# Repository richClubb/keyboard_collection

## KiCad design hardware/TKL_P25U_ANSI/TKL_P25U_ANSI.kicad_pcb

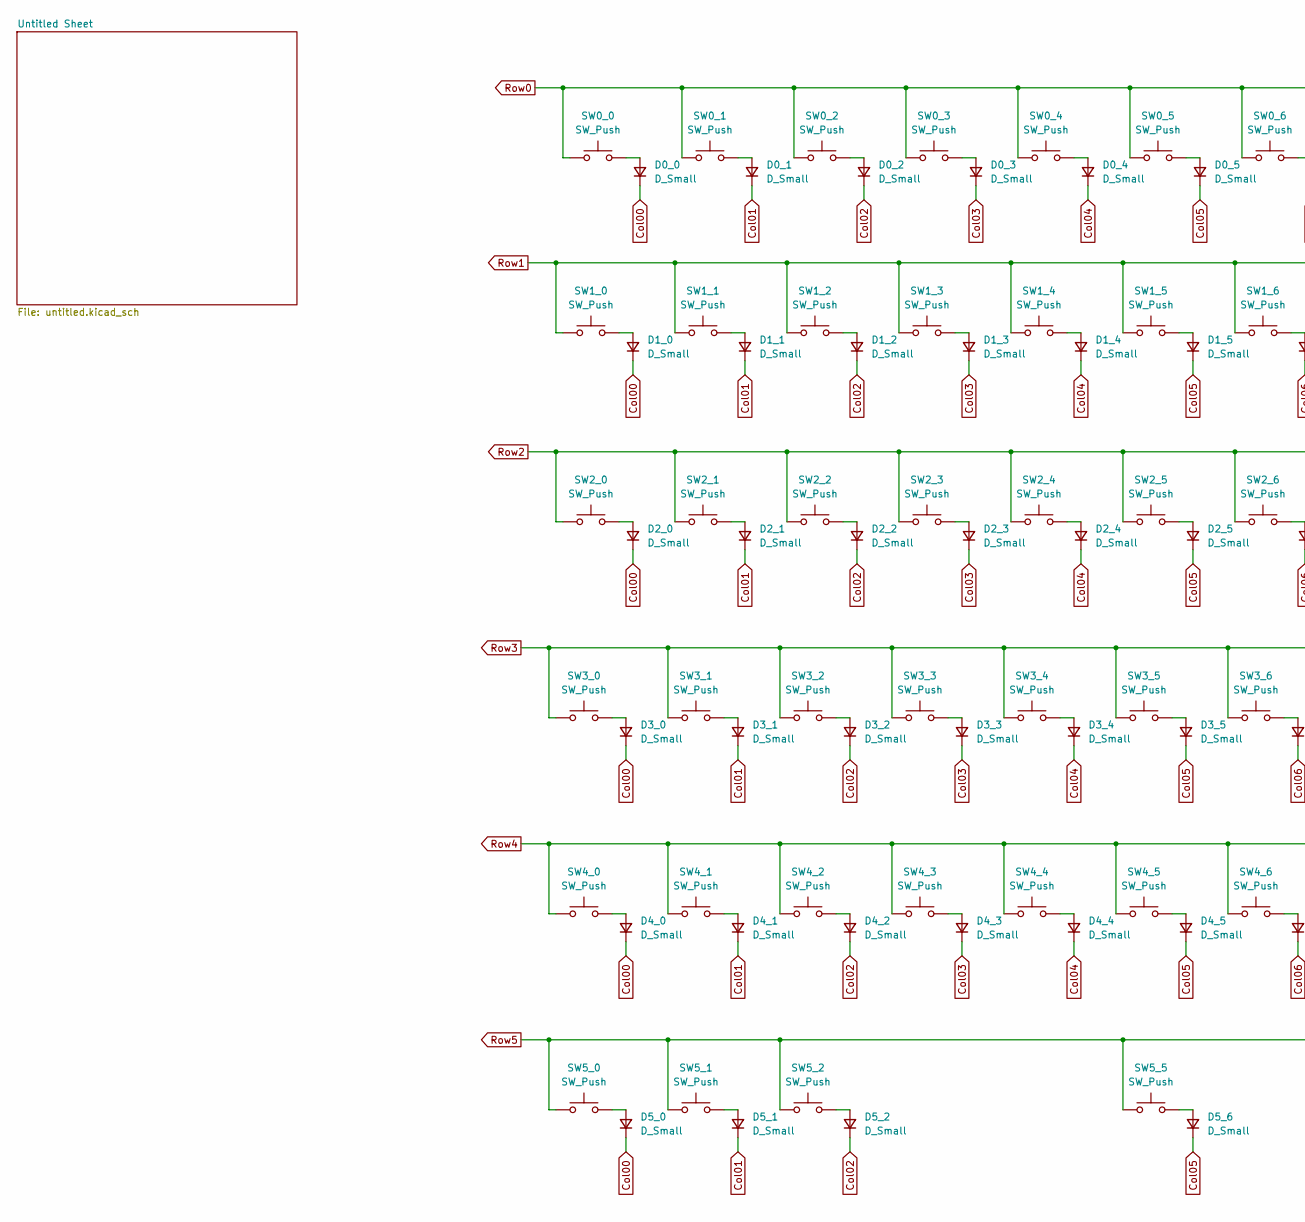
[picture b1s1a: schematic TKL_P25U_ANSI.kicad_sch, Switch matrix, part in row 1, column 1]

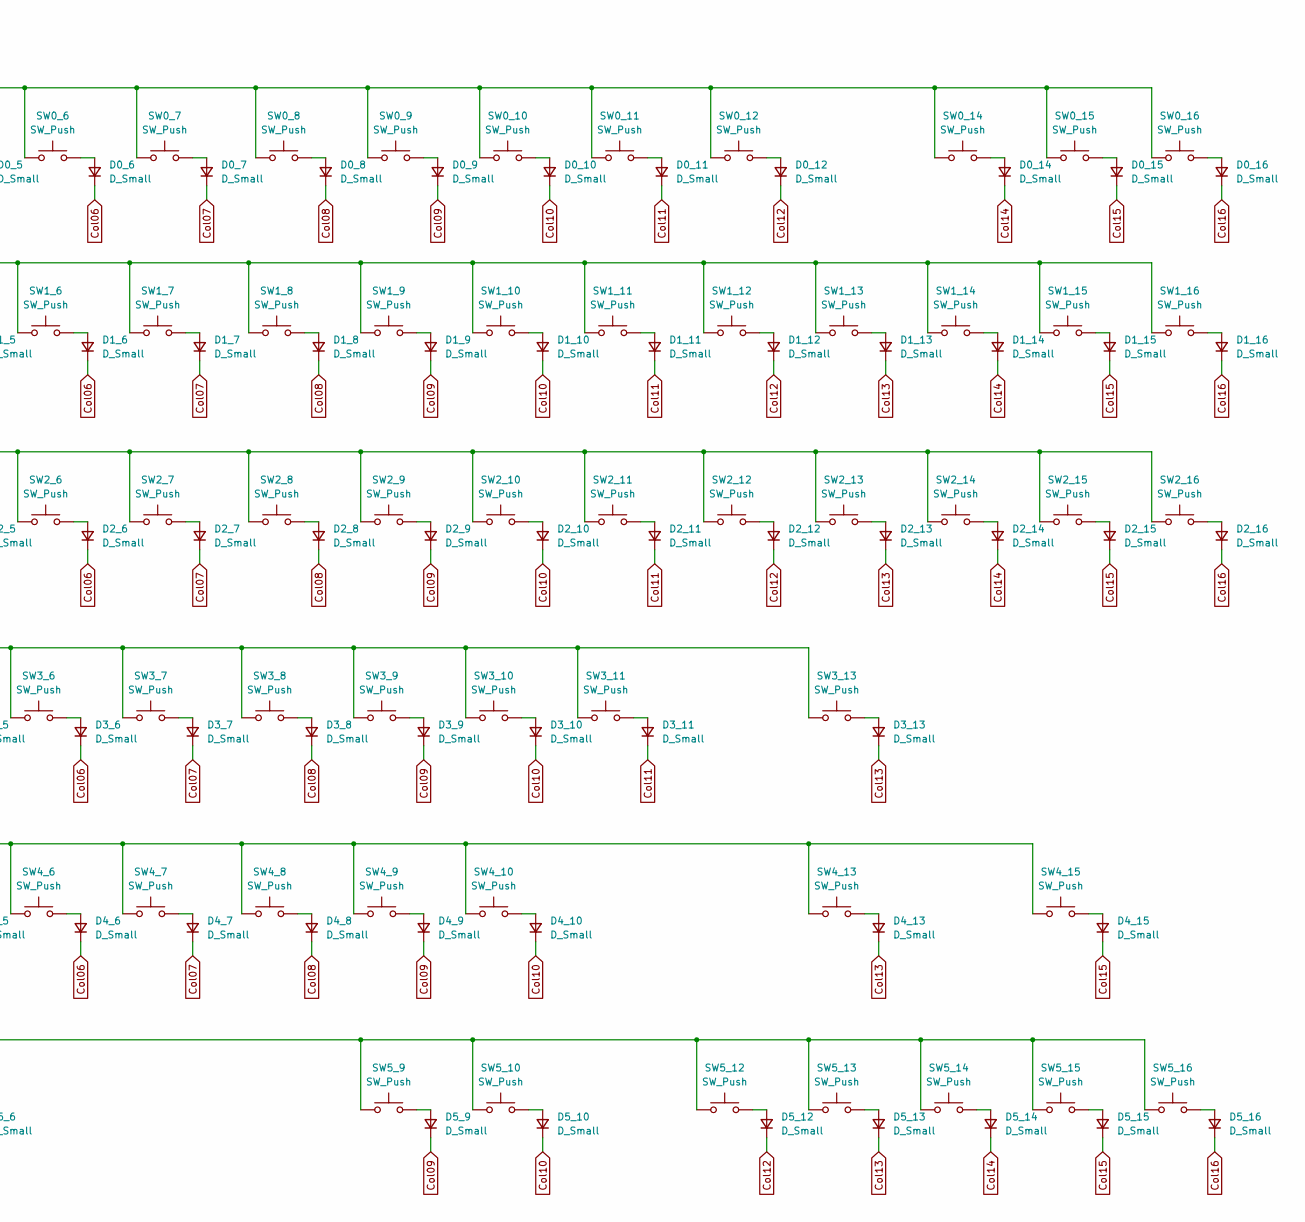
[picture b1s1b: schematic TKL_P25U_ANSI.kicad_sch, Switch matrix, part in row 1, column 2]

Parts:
D0_0, D0_1, D0_2, D0_3, D0_4, D0_5, D0_6, D0_7, D0_8, D0_9, D0_10, D0_11, D0_12, D0_14, D0_15, D0_16, D1_0, D1_1, D1_2, D1_3, D1_4, D1_5, D1_6, D1_7, D1_8, D1_9, D1_10, D1_11, D1_12, D1_13, D1_14, D1_15, D1_16, D2_0, D2_1, D2_2, D2_3, D2_4, D2_5, D2_6, D2_7, D2_8, D2_9, D2_10, D2_11, D2_12, D2_13, D2_14, D2_15, D2_16, D3_0, D3_1, D3_2, D3_3, D3_4, D3_5, D3_6, D3_7, D3_8, D3_9, D3_10, D3_11, D3_13, D4_0, D4_1, D4_2, D4_3, D4_4, D4_5, D4_6, D4_7, D4_8, D4_9, D4_10, D4_13, D4_15, D5_0, D5_1, D5_2, D5_6, D5_9, D5_10, D5_12, D5_13, D5_14, D5_15, D5_16: D_Small; D_0603_1608Metric
SW0_0, SW0_1, SW0_2, SW0_3, SW0_4, SW0_5, SW0_6, SW0_7, SW0_8, SW0_9, SW0_10, SW0_11, SW0_12, SW0_14, SW0_15, SW0_16, SW1_0, SW1_1, SW1_2, SW1_3, SW1_4, SW1_5, SW1_6, SW1_7, SW1_8, SW1_9, SW1_10, SW1_11, SW1_12, SW1_14, SW1_15, SW1_16, SW2_1, SW2_2, SW2_3, SW2_4, SW2_5, SW2_6, SW2_7, SW2_8, SW2_9, SW2_10, SW2_11, SW2_12, SW2_14, SW2_15, SW2_16, SW3_1, SW3_2, SW3_3, SW3_4, SW3_5, SW3_6, SW3_7, SW3_8, SW3_9, SW3_10, SW3_11, SW4_1, SW4_2, SW4_3, SW4_4, SW4_5, SW4_6, SW4_7, SW4_8, SW4_9, SW4_10, SW4_15, SW5_14, SW5_15, SW5_16: SW_Push; SW_Cherry_MX_1.00u_PCB
SW1_13, SW4_0: SW_Push; SW_Cherry_MX_2.00u_PCB
SW2_0, SW2_13: SW_Push; SW_Cherry_MX_1.50u_PCB
SW3_0: SW_Push; SW_Cherry_MX_1.75u_PCB
SW3_13: SW_Push; SW_Cherry_MX_2.25u_PCB
SW4_13: SW_Push; SW_Cherry_MX_2.75u_PCB
SW5_0, SW5_1, SW5_2, SW5_9, SW5_10, SW5_12, SW5_13: SW_Push; SW_Cherry_MX_1.25u_PCB
SW5_5: SW_Push; SW_Cherry_MX_6.25u_PCB

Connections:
Col00: D0_0.1 (K), D1_0.1 (K), D2_0.1 (K), D3_0.1 (K), D4_0.1 (K), D5_0.1 (K); also elsewhere on the board
Col01: D0_1.1 (K), D1_1.1 (K), D2_1.1 (K), D3_1.1 (K), D4_1.1 (K), D5_1.1 (K); also elsewhere on the board
Col02: D0_2.1 (K), D1_2.1 (K), D2_2.1 (K), D3_2.1 (K), D4_2.1 (K), D5_2.1 (K); also elsewhere on the board
Col03: D0_3.1 (K), D1_3.1 (K), D2_3.1 (K), D3_3.1 (K), D4_3.1 (K); also elsewhere on the board
Col04: D0_4.1 (K), D1_4.1 (K), D2_4.1 (K), D3_4.1 (K), D4_4.1 (K); also elsewhere on the board
Col05: D0_5.1 (K), D1_5.1 (K), D2_5.1 (K), D3_5.1 (K), D4_5.1 (K), D5_6.1 (K); also elsewhere on the board
Col06: D0_6.1 (K), D1_6.1 (K), D2_6.1 (K), D3_6.1 (K), D4_6.1 (K); also elsewhere on the board
Col07: D0_7.1 (K), D1_7.1 (K), D2_7.1 (K), D3_7.1 (K), D4_7.1 (K); also elsewhere on the board
Col08: D0_8.1 (K), D1_8.1 (K), D2_8.1 (K), D3_8.1 (K), D4_8.1 (K); also elsewhere on the board
Col09: D0_9.1 (K), D1_9.1 (K), D2_9.1 (K), D3_9.1 (K), D4_9.1 (K), D5_9.1 (K); also elsewhere on the board
Col10: D0_10.1 (K), D1_10.1 (K), D2_10.1 (K), D3_10.1 (K), D4_10.1 (K), D5_10.1 (K); also elsewhere on the board
Col11: D0_11.1 (K), D1_11.1 (K), D2_11.1 (K), D3_11.1 (K); also elsewhere on the board
Col12: D0_12.1 (K), D1_12.1 (K), D2_12.1 (K), D5_12.1 (K); also elsewhere on the board
Col13: D1_13.1 (K), D2_13.1 (K), D3_13.1 (K), D4_13.1 (K), D5_13.1 (K); also elsewhere on the board
Col14: D0_14.1 (K), D1_14.1 (K), D2_14.1 (K), D5_14.1 (K); also elsewhere on the board
Col15: D0_15.1 (K), D1_15.1 (K), D2_15.1 (K), D4_15.1 (K), D5_15.1 (K); also elsewhere on the board
Col16: D0_16.1 (K), D1_16.1 (K), D2_16.1 (K), D5_16.1 (K); also elsewhere on the board
unnamed: D0_0.2 (A), SW0_0.2
unnamed: D0_1.2 (A), SW0_1.2
unnamed: D0_2.2 (A), SW0_2.2
unnamed: D0_3.2 (A), SW0_3.2
unnamed: D0_4.2 (A), SW0_4.2
unnamed: D0_5.2 (A), SW0_5.2
unnamed: D0_6.2 (A), SW0_6.2
unnamed: D0_7.2 (A), SW0_7.2
unnamed: D0_8.2 (A), SW0_8.2
unnamed: D0_9.2 (A), SW0_9.2
unnamed: D0_10.2 (A), SW0_10.2
unnamed: D0_11.2 (A), SW0_11.2
unnamed: D0_12.2 (A), SW0_12.2
unnamed: D0_14.2 (A), SW0_14.2
unnamed: D0_15.2 (A), SW0_15.2
unnamed: D0_16.2 (A), SW0_16.2
unnamed: D1_0.2 (A), SW1_0.2
unnamed: D1_1.2 (A), SW1_1.2
unnamed: D1_2.2 (A), SW1_2.2
unnamed: D1_3.2 (A), SW1_3.2
unnamed: D1_4.2 (A), SW1_4.2
unnamed: D1_5.2 (A), SW1_5.2
unnamed: D1_6.2 (A), SW1_6.2
unnamed: D1_7.2 (A), SW1_7.2
unnamed: D1_8.2 (A), SW1_8.2
unnamed: D1_9.2 (A), SW1_9.2
unnamed: D1_10.2 (A), SW1_10.2
unnamed: D1_11.2 (A), SW1_11.2
unnamed: D1_12.2 (A), SW1_12.2
unnamed: D1_13.2 (A), SW1_13.2
unnamed: D1_14.2 (A), SW1_14.2
unnamed: D1_15.2 (A), SW1_15.2
unnamed: D1_16.2 (A), SW1_16.2
unnamed: D2_0.2 (A), SW2_0.2
unnamed: D2_1.2 (A), SW2_1.2
unnamed: D2_2.2 (A), SW2_2.2
unnamed: D2_3.2 (A), SW2_3.2
unnamed: D2_4.2 (A), SW2_4.2
unnamed: D2_5.2 (A), SW2_5.2
unnamed: D2_6.2 (A), SW2_6.2
unnamed: D2_7.2 (A), SW2_7.2
unnamed: D2_8.2 (A), SW2_8.2
unnamed: D2_9.2 (A), SW2_9.2
unnamed: D2_10.2 (A), SW2_10.2
unnamed: D2_11.2 (A), SW2_11.2
unnamed: D2_12.2 (A), SW2_12.2
unnamed: D2_13.2 (A), SW2_13.2
unnamed: D2_14.2 (A), SW2_14.2
unnamed: D2_15.2 (A), SW2_15.2
unnamed: D2_16.2 (A), SW2_16.2
unnamed: D3_0.2 (A), SW3_0.2
unnamed: D3_1.2 (A), SW3_1.2
unnamed: D3_2.2 (A), SW3_2.2
unnamed: D3_3.2 (A), SW3_3.2
unnamed: D3_4.2 (A), SW3_4.2
unnamed: D3_5.2 (A), SW3_5.2
unnamed: D3_6.2 (A), SW3_6.2
unnamed: D3_7.2 (A), SW3_7.2
unnamed: D3_8.2 (A), SW3_8.2
unnamed: D3_9.2 (A), SW3_9.2
unnamed: D3_10.2 (A), SW3_10.2
unnamed: D3_11.2 (A), SW3_11.2
unnamed: D3_13.2 (A), SW3_13.2
unnamed: D4_0.2 (A), SW4_0.2
unnamed: D4_1.2 (A), SW4_1.2
unnamed: D4_2.2 (A), SW4_2.2
unnamed: D4_3.2 (A), SW4_3.2
unnamed: D4_4.2 (A), SW4_4.2
unnamed: D4_5.2 (A), SW4_5.2
unnamed: D4_6.2 (A), SW4_6.2
unnamed: D4_7.2 (A), SW4_7.2
unnamed: D4_8.2 (A), SW4_8.2
unnamed: D4_9.2 (A), SW4_9.2
unnamed: D4_10.2 (A), SW4_10.2
unnamed: D4_13.2 (A), SW4_13.2
unnamed: D4_15.2 (A), SW4_15.2
unnamed: D5_0.2 (A), SW5_0.2
unnamed: D5_1.2 (A), SW5_1.2
unnamed: D5_2.2 (A), SW5_2.2
unnamed: D5_6.2 (A), SW5_5.2
unnamed: D5_9.2 (A), SW5_9.2
unnamed: D5_10.2 (A), SW5_10.2
unnamed: D5_12.2 (A), SW5_12.2
unnamed: D5_13.2 (A), SW5_13.2
unnamed: D5_14.2 (A), SW5_14.2
unnamed: D5_15.2 (A), SW5_15.2
unnamed: D5_16.2 (A), SW5_16.2
Row0: SW0_0.1, SW0_1.1, SW0_2.1, SW0_3.1, SW0_4.1, SW0_5.1, SW0_6.1, SW0_7.1, SW0_8.1, SW0_9.1, SW0_10.1, SW0_11.1, SW0_12.1, SW0_14.1, SW0_15.1, SW0_16.1; also elsewhere on the board
Row1: SW1_0.1, SW1_1.1, SW1_2.1, SW1_3.1, SW1_4.1, SW1_5.1, SW1_6.1, SW1_7.1, SW1_8.1, SW1_9.1, SW1_10.1, SW1_11.1, SW1_12.1, SW1_13.1, SW1_14.1, SW1_15.1, SW1_16.1; also elsewhere on the board
Row2: SW2_0.1, SW2_1.1, SW2_2.1, SW2_3.1, SW2_4.1, SW2_5.1, SW2_6.1, SW2_7.1, SW2_8.1, SW2_9.1, SW2_10.1, SW2_11.1, SW2_12.1, SW2_13.1, SW2_14.1, SW2_15.1, SW2_16.1; also elsewhere on the board
Row3: SW3_0.1, SW3_1.1, SW3_2.1, SW3_3.1, SW3_4.1, SW3_5.1, SW3_6.1, SW3_7.1, SW3_8.1, SW3_9.1, SW3_10.1, SW3_11.1, SW3_13.1; also elsewhere on the board
Row4: SW4_0.1, SW4_1.1, SW4_2.1, SW4_3.1, SW4_4.1, SW4_5.1, SW4_6.1, SW4_7.1, SW4_8.1, SW4_9.1, SW4_10.1, SW4_13.1, SW4_15.1; also elsewhere on the board
Row5: SW5_0.1, SW5_1.1, SW5_2.1, SW5_5.1, SW5_9.1, SW5_10.1, SW5_12.1, SW5_13.1, SW5_14.1, SW5_15.1, SW5_16.1; also elsewhere on the board

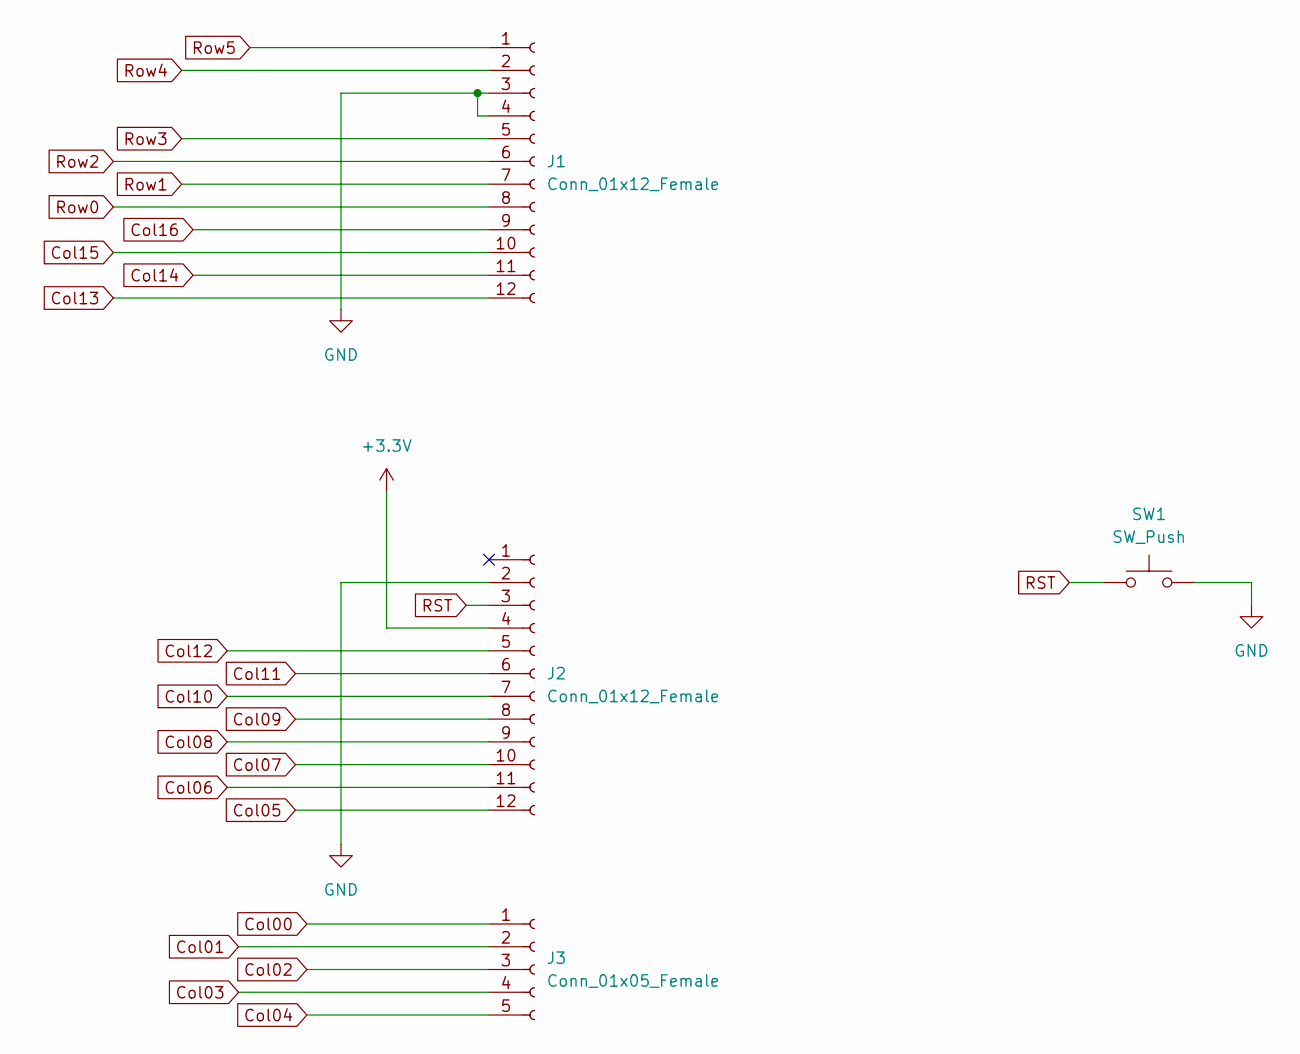
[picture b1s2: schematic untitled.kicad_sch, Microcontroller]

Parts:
J1, J2: Conn_01x12_Female; PinSocket_1x12_P2.54mm_Vertical
J3: Conn_01x05_Female; PinSocket_1x05_P2.54mm_Vertical
SW1: SW_Push; SW_PUSH_6mm

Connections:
+3V3: J2.4
Col00: J3.1; also elsewhere on the board
Col01: J3.2; also elsewhere on the board
Col02: J3.3; also elsewhere on the board
Col03: J3.4; also elsewhere on the board
Col04: J3.5; also elsewhere on the board
Col05: J2.12; also elsewhere on the board
Col06: J2.11; also elsewhere on the board
Col07: J2.10; also elsewhere on the board
Col08: J2.9; also elsewhere on the board
Col09: J2.8; also elsewhere on the board
Col10: J2.7; also elsewhere on the board
Col11: J2.6; also elsewhere on the board
Col12: J2.5; also elsewhere on the board
Col13: J1.12; also elsewhere on the board
Col14: J1.11; also elsewhere on the board
Col15: J1.10; also elsewhere on the board
Col16: J1.9; also elsewhere on the board
GND: J1.3, J1.4, J2.2, SW1.2
RST: J2.3, SW1.1
Row0: J1.8; also elsewhere on the board
Row1: J1.7; also elsewhere on the board
Row2: J1.6; also elsewhere on the board
Row3: J1.5; also elsewhere on the board
Row4: J1.2; also elsewhere on the board
Row5: J1.1; also elsewhere on the board

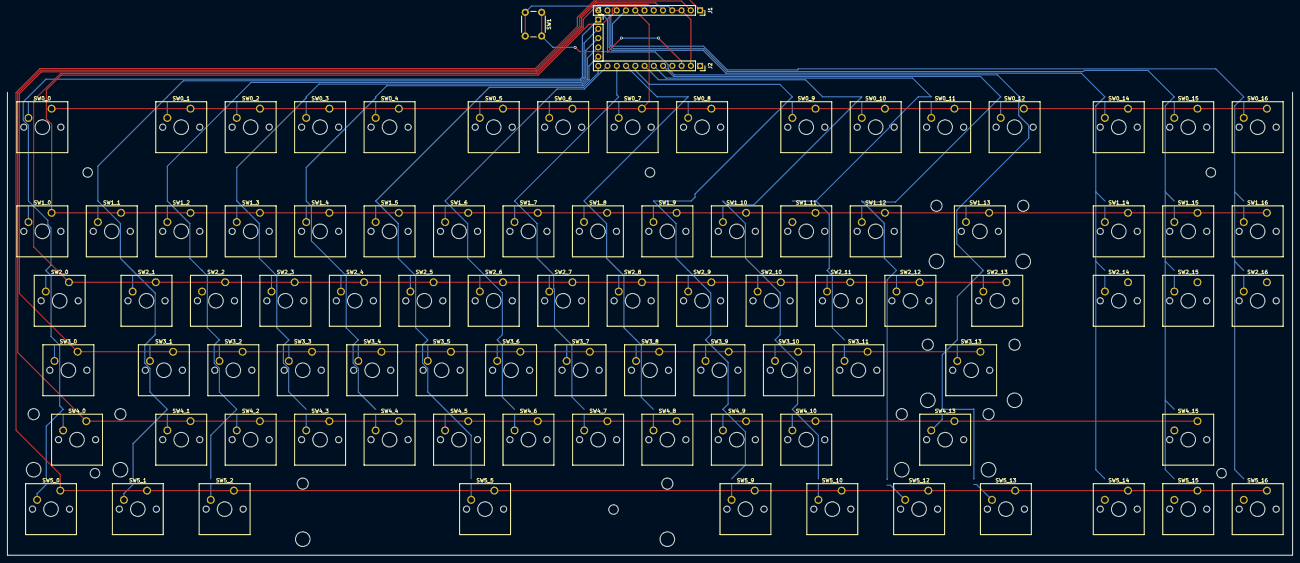
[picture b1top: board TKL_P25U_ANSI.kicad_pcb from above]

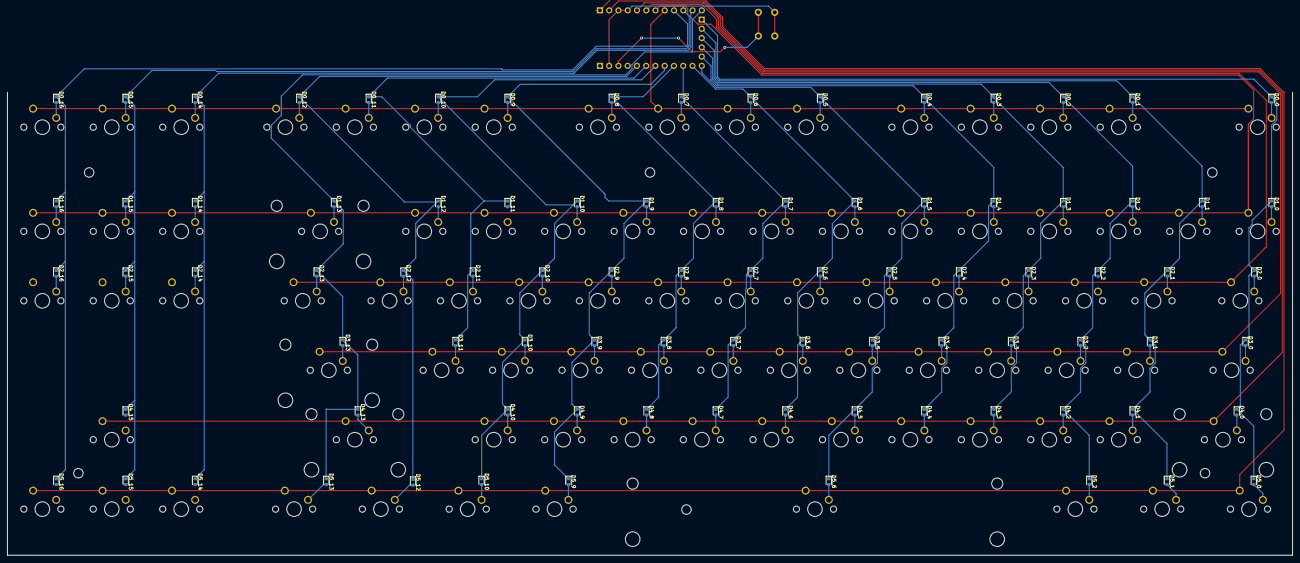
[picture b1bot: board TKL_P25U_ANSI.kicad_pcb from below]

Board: 2 copper layers, 352.5 x 127.0 mm, 178 parts (87 on the bottom side), 112 nets.

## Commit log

2022-10-12 initial
